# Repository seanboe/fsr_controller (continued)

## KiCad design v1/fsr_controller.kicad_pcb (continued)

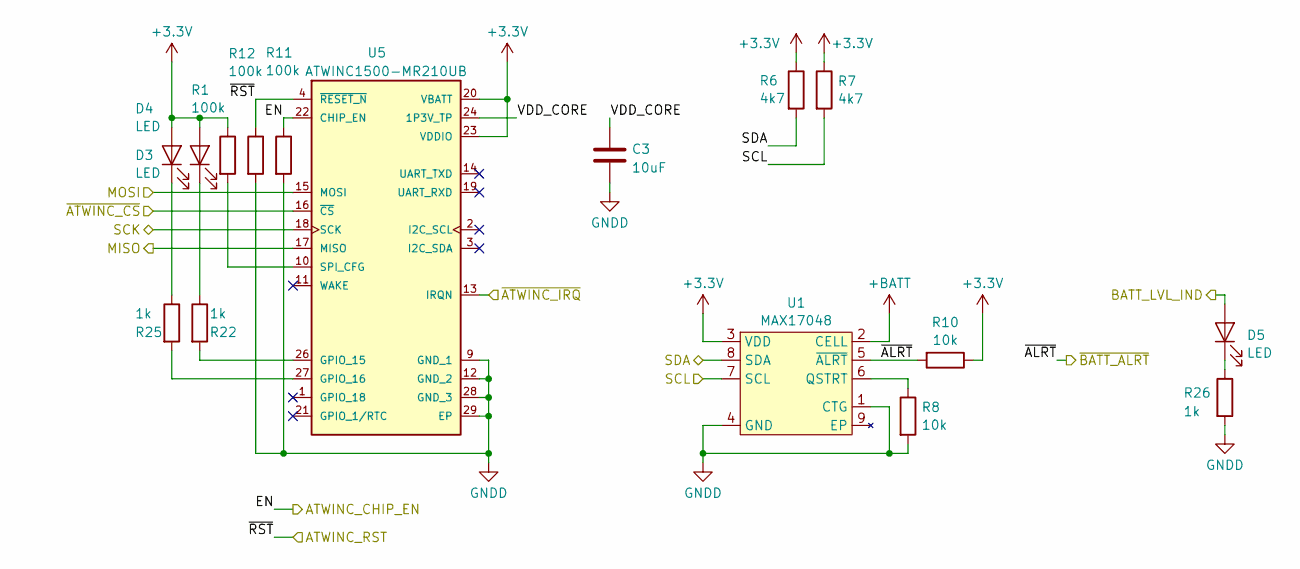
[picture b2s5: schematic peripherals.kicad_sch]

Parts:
C3: 10uF; C_1608_603_B
D3, D4, D5: LED; D_0603
R1, R11, R12: 100k; R_1608_603_B
R6, R7: 4k7; R_1608_603_B
R8, R10: 10k; R_1608_603_B
R22, R25, R26: 1k; R_1608_603_B
U1: MAX17048; DFN-8-1EP_2x2mm_P0.5mm_EP0.9x1.5mm
U5: ATWINC1500-MR210UB; MICROCHIP_ATWINC1500-MR210UB

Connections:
+3.3V: D3.2 (A), D4.2 (A), R1.1, R6.1, R7.1, R10.1, U1.3 (VDD), U5.20 (VBATT), U5.23 (VDDIO); also elsewhere on the board
+BATT: U1.2 (CELL); also elsewhere on the board
/ATWINC_CHIP_EN: R11.1, U5.22 (CHIP_EN); also elsewhere on the board
/ATWINC_RST: R12.1, U5.4 (~RESET_N); also elsewhere on the board
/BATT_LVL_IND: D5.2 (A); also elsewhere on the board
/MISO: U5.17 (MISO); also elsewhere on the board
/MOSI: U5.15 (MOSI); also elsewhere on the board
/SCK: U5.18 (SCK); also elsewhere on the board
/SCL: R7.2, U1.7 (SCL); also elsewhere on the board
/SDA: R6.2, U1.8 (SDA); also elsewhere on the board
/peripherals/VDD_CORE: C3.2, U5.24 (1P3V_TP)
/~ATWINC_CS: U5.16 (~CS); also elsewhere on the board
/~ATWINC_IRQ: U5.13 (IRQN); also elsewhere on the board
/~BATT_ALRT: R10.2, U1.5 (~ALRT); also elsewhere on the board
GNDD: C3.1, R8.2, R11.2, R12.2, R26.2, U1.1 (CTG), U1.4 (GND), U5.9 (GND_1), U5.12 (GND_2), U5.28 (GND_3), U5.29 (EP); also elsewhere on the board
unnamed: D3.1 (K), R22.1
unnamed: D4.1 (K), R25.1
unnamed: D5.1 (K), R26.1
unnamed: R8.1, U1.6 (QSTRT)
unnamed: R22.2, U5.26 (GPIO_15)
unnamed: R25.2, U5.27 (GPIO_16)
unnamed: R1.2, U5.10 (SPI_CFG)

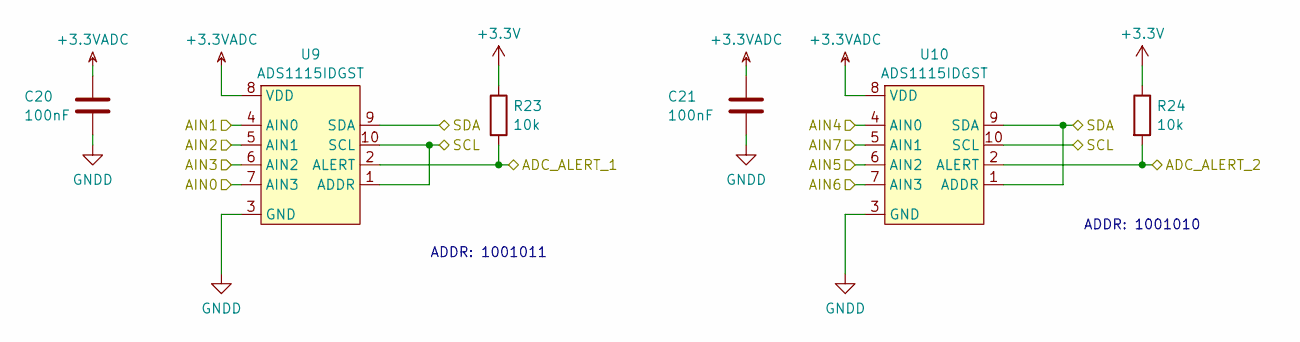
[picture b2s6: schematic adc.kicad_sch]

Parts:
C20, C21: 100nF; C_1608_603_B
R23, R24: 10k; R_1608_603_B
U9, U10: ADS1115IDGST; VSSOP-10_3x3mm_P0.5mm

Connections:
+3.3V: R23.1, R24.1; also elsewhere on the board
+3.3VADC: C20.1, C21.1, U9.8 (VDD), U10.8 (VDD); also elsewhere on the board
/ADC_ALERT_1: R23.2, U9.2 (ALERT); also elsewhere on the board
/ADC_ALERT_2: R24.2, U10.2 (ALERT); also elsewhere on the board
/SCL: U9.1 (ADDR), U9.10 (SCL), U10.10 (SCL); also elsewhere on the board
/SDA: U9.9 (SDA), U10.1 (ADDR), U10.9 (SDA); also elsewhere on the board
/adc/AIN0: U9.7 (AIN3); also elsewhere on the board
/adc/AIN1: U9.4 (AIN0); also elsewhere on the board
/adc/AIN2: U9.5 (AIN1); also elsewhere on the board
/adc/AIN3: U9.6 (AIN2); also elsewhere on the board
/adc/AIN4: U10.4 (AIN0); also elsewhere on the board
/adc/AIN5: U10.6 (AIN2); also elsewhere on the board
/adc/AIN6: U10.7 (AIN3); also elsewhere on the board
/adc/AIN7: U10.5 (AIN1); also elsewhere on the board
GNDD: C20.2, C21.2, U9.3 (GND), U10.3 (GND); also elsewhere on the board

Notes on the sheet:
ADDR: 1001010
ADDR: 1001011

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
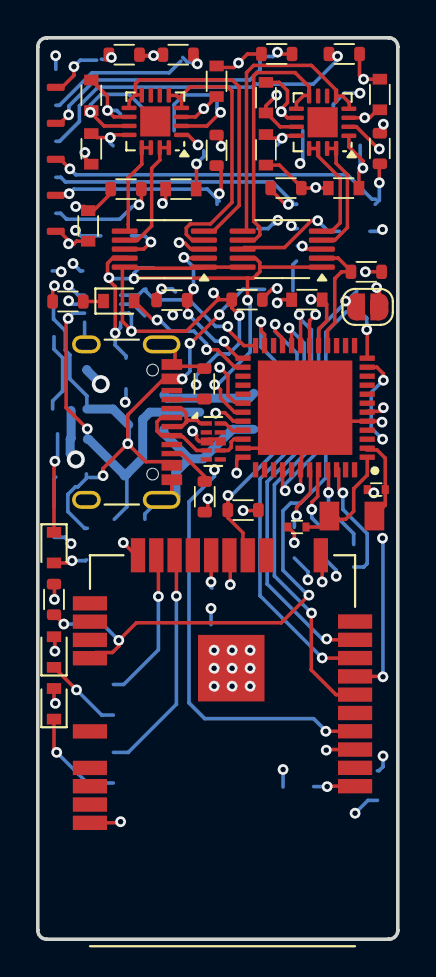
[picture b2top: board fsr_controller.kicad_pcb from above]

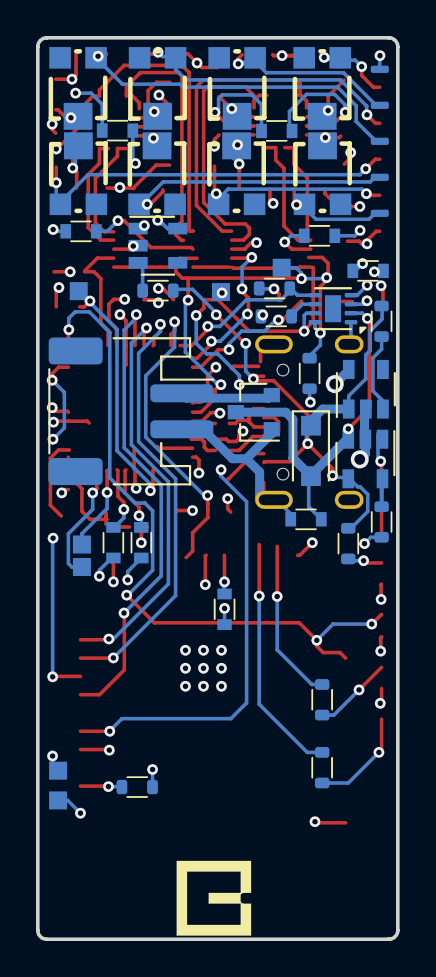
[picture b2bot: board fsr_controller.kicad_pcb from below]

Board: 4 copper layers, 20.0 x 50.1 mm, 84 parts (41 on the bottom side), 68 nets.

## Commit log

2024-06-18 rheostats kidna working
2024-06-20 streamign to computer working
2024-11-25 added scripts
2025-02-23 updated library
